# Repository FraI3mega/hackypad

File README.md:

# Hackypad

A simple little 8-key macropad based on the RP2040 running qmk firmware

## See it in action

## Features

- 8 Programmable keys
- EC11 Encoder
- 128x32 OLED Display

## CAD Model

## PCB

### Schematic

## Firmware

The firmware is set up with a basic keymap.
The display should also work, though I will have to test it.
Might switch to the RMK frimware in the future.

## BOM

| Item                | Qnt |
|-------------------- | --- |
| Xiao RP2040         | 1   |
| EC11 Encoder        | 1   |
| 0.91" OLED Display  | 1   |
| MX Switch           | 8   |
| 1N4148 Diode        | 9   |
| DSA Keycap          | 8   |
| M3 Screw            | 4   |

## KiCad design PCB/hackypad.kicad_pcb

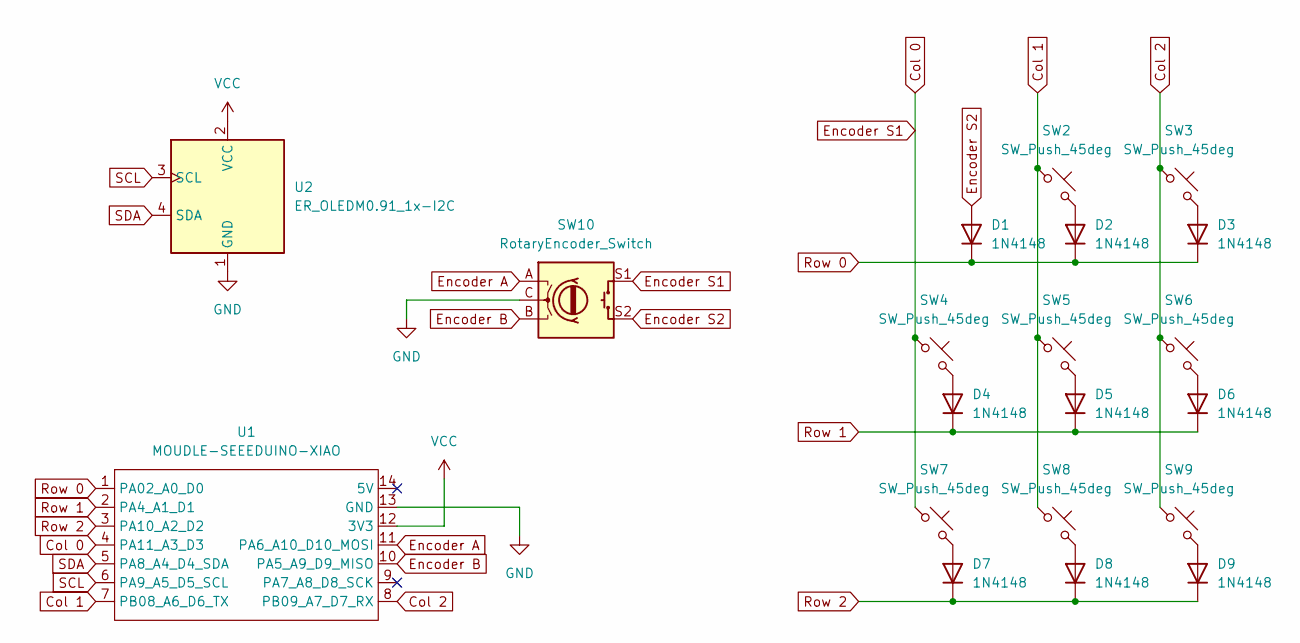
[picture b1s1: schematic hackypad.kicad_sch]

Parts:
D1, D2, D3, D4, D5, D6, D7, D8, D9: 1N4148; D_DO-35_SOD27_P7.62mm_Horizontal
SW2, SW3, SW4, SW5, SW6, SW7, SW8, SW9: SW_Push_45deg; SW_Cherry_MX_1.00u_PCB
SW10: RotaryEncoder_Switch; RotaryEncoder_Alps_EC11E-Switch_Vertical_H20mm
U1: MOUDLE-SEEEDUINO-XIAO; XIAO-Generic-Hybrid-14P-2.54-21X17.8MM
U2: ER_OLEDM0.91_1x-I2C

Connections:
Col 0: SW4.1, SW7.1, SW10.S1, U1.4 (PA11_A3_D3)
Col 1: SW2.1, SW5.1, SW8.1, U1.7 (PB08_A6_D6_TX)
Col 2: SW3.1, SW6.1, SW9.1, U1.8 (PB09_A7_D7_RX)
Encoder A: SW10.A, U1.11 (PA6_A10_D10_MOSI)
Encoder B: SW10.B, U1.10 (PA5_A9_D9_MISO)
Encoder S2: D1.2 (A), SW10.S2
GND: SW10.C, U1.13 (GND), U2.1 (GND)
unnamed: D2.2 (A), SW2.2
unnamed: D3.2 (A), SW3.2
unnamed: D4.2 (A), SW4.2
unnamed: D5.2 (A), SW5.2
unnamed: D6.2 (A), SW6.2
unnamed: D7.2 (A), SW7.2
unnamed: D8.2 (A), SW8.2
unnamed: D9.2 (A), SW9.2
Row 0: D1.1 (K), D2.1 (K), D3.1 (K), U1.1 (PA02_A0_D0)
Row 1: D4.1 (K), D5.1 (K), D6.1 (K), U1.2 (PA4_A1_D1)
Row 2: D7.1 (K), D8.1 (K), D9.1 (K), U1.3 (PA10_A2_D2)
SCL: U1.6 (PA9_A5_D5_SCL), U2.3 (SCL)
SDA: U1.5 (PA8_A4_D4_SDA), U2.4 (SDA)
VCC: U1.12 (3V3), U2.2 (VCC)

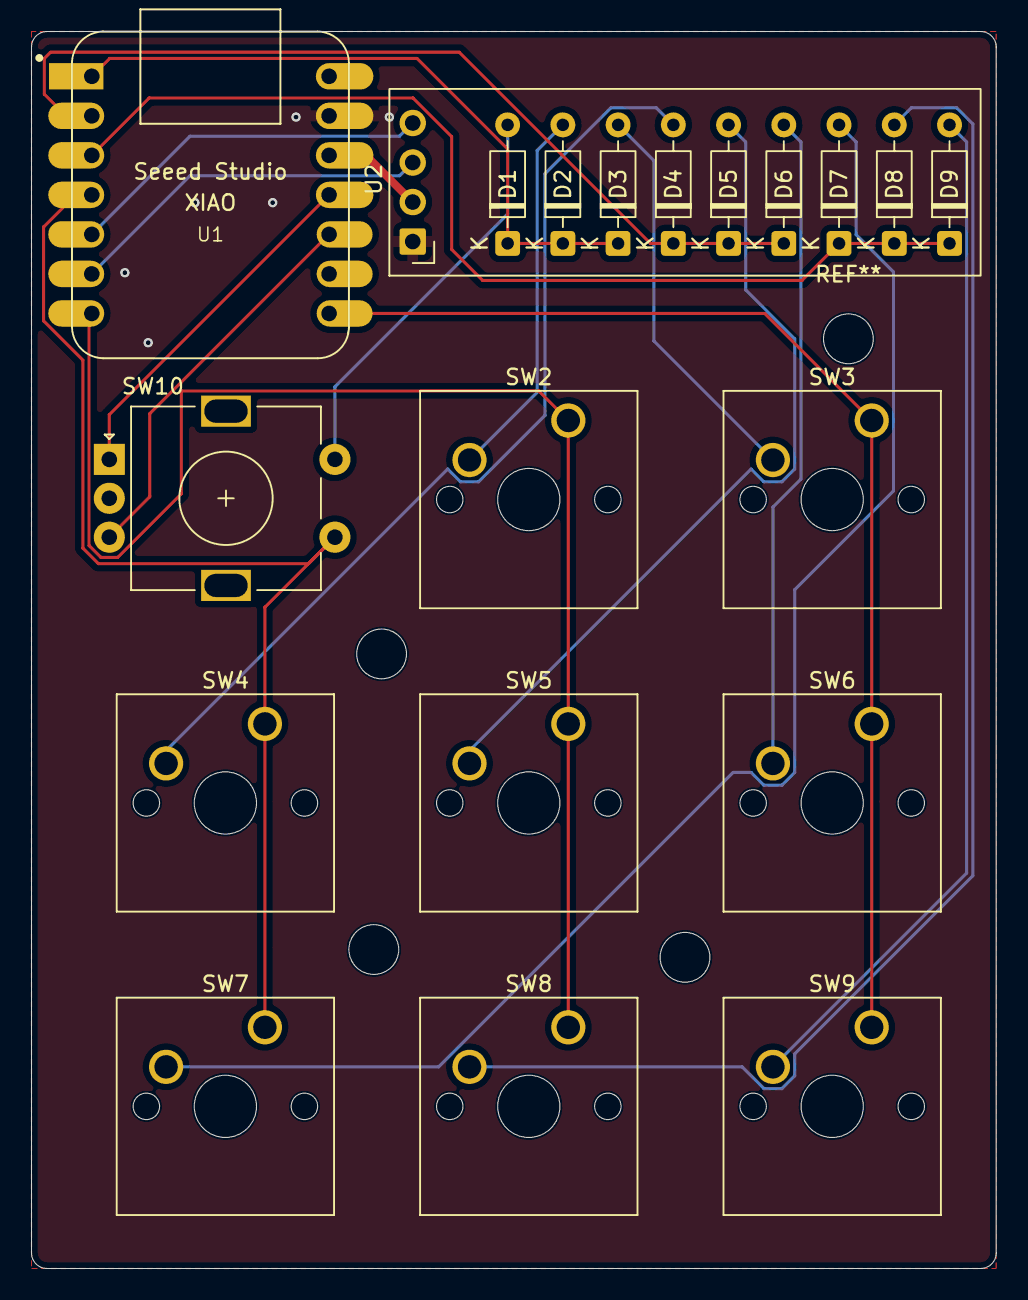
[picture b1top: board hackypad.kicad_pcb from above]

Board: 2 copper layers, 62.0 x 79.5 mm, 20 parts (0 on the bottom side), 21 nets.
